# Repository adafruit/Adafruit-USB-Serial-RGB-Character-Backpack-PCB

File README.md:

## Adafruit USB Serial RGB Character Backpack PCB
&nbsp; 
<br/>
Click the image or links below to go to a specific product in the Adafruit shop.

PCB files for the Adafruit USB Serial RGB Character Backpack. Format is EagleCAD schematic and board layout
- Positive Backlight https://www.adafruit.com/product/782
- Negative Backlight https://www.adafruit.com/product/784

### DESCRIPTION
Adding a character display to your project or computer has never been easier with the new Adafruit USB or TTL serial backpack! This custom-designed PCB sits on the back of our 'standard' character LCD (16x2 or 20x4 sized) and does everything you could want: printing text, automatic scrolling, setting the backlight, adjusting contrast, making custom characters, turning on and off the cursor, etc. It can even handle our RGB backlight LCDs with full 8-bit PWM control of the backlight. That means you can change the background color to anything you want - red, green, blue, pink, white, purple yellow, teal, salmon, chartreuse, or just leave it off for a neutral background.

Inside the backpack is an USB-capable AT90USB162 chip that listens for commands both a mini-B USB port and a TTL serial input wire. The USB interface shows up as a COM/serial port on Windows/Mac/Linux. The backpack will automatically select data from whichever input is being used. For the USB connection, it will work at any baud rate. For the TTL connection, the default baud rate is 9600 but you can send it a command to set the baud rate to 2400, 4800, 9600, 19200, 28800, or 57600 baud. (The baud rate is flashed on the LCD during powerup). Any customizations such as baud rate, backlight color, brightness, splash screen, etc. are stored permanently EEPROM.

The command interface is compatible with the popular "Matrix Orbital" specifications, so this backpack will work perfectly with computer applications or libraries that are expecting a "Matrix" LCD such as "LCD Smartie". We added a few extra commands for the RGB backlight and setting the LCD size. If you don't want to use the commands, you can just start sending ASCII to the LCD and it will magically appear as typed.

This mini-kit comes with three parts: the Adafruit USB+Serial LCD backpack and a single 16x2 RGB positive or negative backlight LCD, and a strip of header. The LCD must be soldered onto the backpack using the header. This isn't a difficult task but a soldering iron and solder is required. It's easy, even for a beginner, to attach the LCD.

### License

Adafruit invests time and resources providing this open source design, please support Adafruit and open-source hardware by purchasing products from [Adafruit.com](https://www.adafruit.com)!

Creative Commons Attribution, Share-Alike license, check license.txt for more information All text above must be included in any redistribution - 
See license.txt for more information.

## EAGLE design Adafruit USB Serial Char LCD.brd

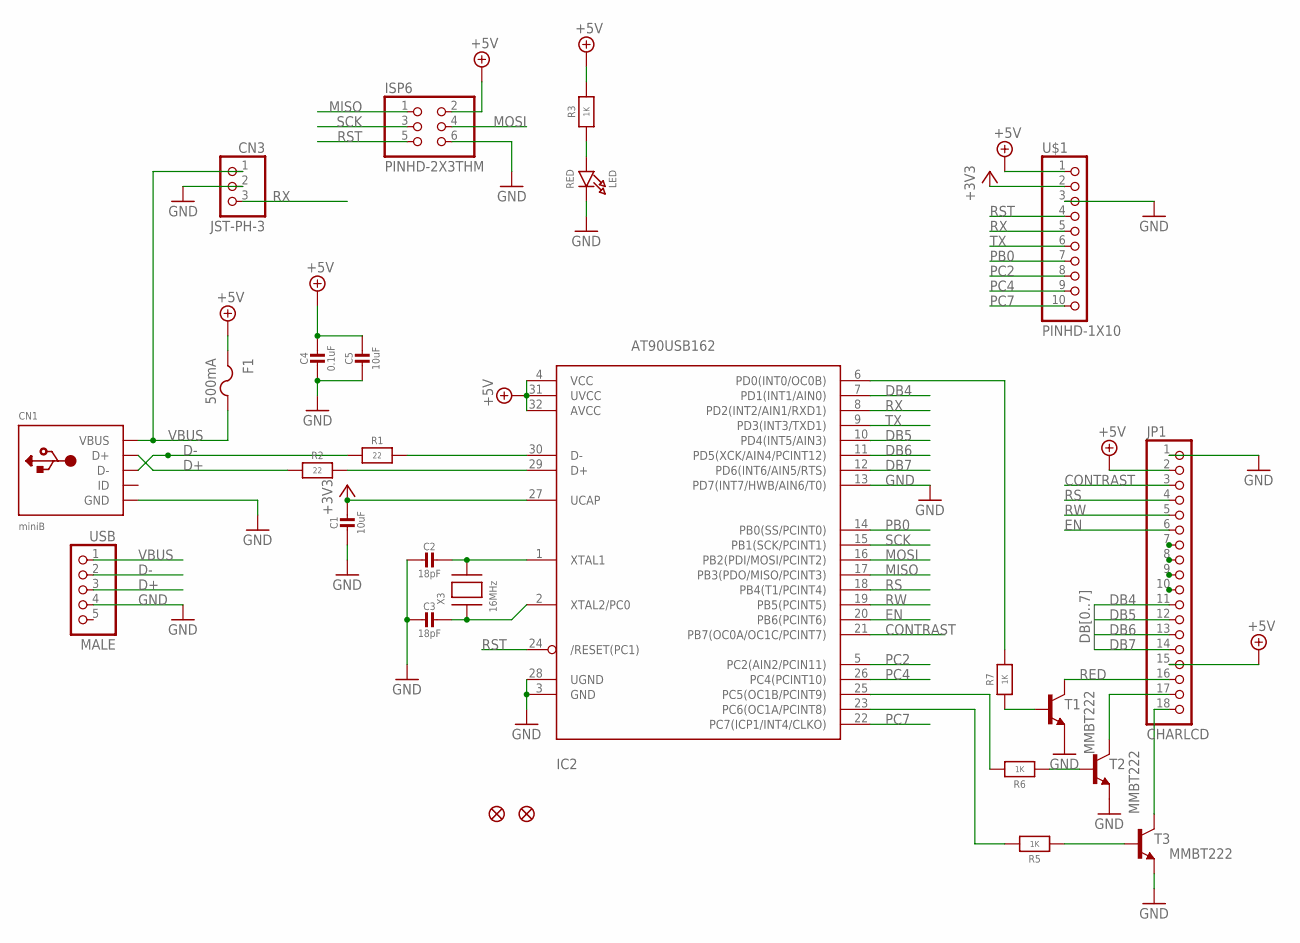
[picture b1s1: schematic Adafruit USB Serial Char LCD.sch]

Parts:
C1, C5: 10uF; 0805-NO
C2, C3: 18pF; 0805-NO
C4: 0.1uF; 0805-NO
CN1: miniB; USB-MINIB_LARGER
CN3: JST-PH-3; JSTPH3
F1: 500mA; R1206
FID1, FID2: FIDUCIAL1X2.5; FIDUCIAL-1X2.5
IC2: AT90USB162; TQFP32-08
ISP6: PINHD-2X3THM; ISP6
JP1: CHARLCD; 1X18-BIG
LED: RED; CHIPLED_0805_NOOUTLINE
R1, R2: 22; 0805-NO
R3, R5, R6, R7: 1K; 0805-NO
T1, T2, T3: MMBT222; SOT23-BEC
U$1: PINHD-1X10; 1X10-BIG
USB: MALE; 1X05
X3: 16MHz; NX5032

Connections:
+3V3: C1.1, IC2.27 (UCAP), U$1.2
+5V: C4.1, C5.1, F1.1, IC2.4 (VCC), IC2.31 (UVCC), IC2.32 (AVCC), ISP6.2, JP1.2, JP1.15, R3.2, U$1.1
BLUE: JP1.18, T3.C
CONTRAST: IC2.21 (PB7(OC0A/OC1C/PCINT7)), JP1.3
D+: CN1.D+, R2.1, USB.3
D-: CN1.D-, R1.1, USB.2
DB0: JP1.7
DB1: JP1.8
DB2: JP1.9
DB3: JP1.10
DB4: IC2.7 (PD1(INT1/AIN0)), JP1.11
DB5: IC2.10 (PD4(INT5/AIN3)), JP1.12
DB6: IC2.11 (PD5(XCK/AIN4/PCINT12)), JP1.13
DB7: IC2.12 (PD6(INT6/AIN5/RTS)), JP1.14
EN: IC2.20 (PB6(PCINT6)), JP1.6
GND: C1.2, C2.2, C3.2, C4.2, C5.2, CN1.GND, CN3.2, IC2.3 (GND), IC2.13 (PD7(INT7/HWB/AIN6/T0)), IC2.28 (UGND), ISP6.6, JP1.1, LED.C, T1.E, T2.E, T3.E, U$1.3, USB.4
GREEN: JP1.17, T2.C
MISO: IC2.17 (PB3(PDO/MISO/PCINT3)), ISP6.1
MOSI: IC2.16 (PB2(PDI/MOSI/PCINT2)), ISP6.4
unnamed: LED.A, R3.1
unnamed: R7.1, T1.B
unnamed: IC2.30 (D-), R1.2
unnamed: IC2.29 (D+), R2.2
unnamed: IC2.6 (PD0(INT0/OC0B)), R7.2
unnamed: R6.1, T2.B
unnamed: IC2.25 (PC5(OC1B/PCINT9)), R6.2
unnamed: C2.1, IC2.1 (XTAL1), X3.P$2
unnamed: C3.1, IC2.2 (XTAL2/PC0), X3.P$1
unnamed: IC2.23 (PC6(OC1A/PCINT8)), R5.2
unnamed: R5.1, T3.B
PB0: IC2.14 (PB0(SS/PCINT0)), U$1.7
PC2: IC2.5 (PC2(AIN2/PCIN11)), U$1.8
PC4: IC2.26 (PC4(PCINT10)), U$1.9
PC7: IC2.22 (PC7(ICP1/INT4/CLKO)), U$1.10
RED: JP1.16, T1.C
RS: IC2.18 (PB4(T1/PCINT4)), JP1.4
RST: IC2.24 (/RESET(PC1)), ISP6.5, U$1.4
RW: IC2.19 (PB5(PCINT5)), JP1.5
RX: CN3.3, IC2.8 (PD2(INT2/AIN1/RXD1)), U$1.5
SCK: IC2.15 (PB1(SCK/PCINT1)), ISP6.3
TX: IC2.9 (PD3(INT3/TXD1)), U$1.6
VBUS: CN1.VBUS, CN3.1, F1.2, USB.1

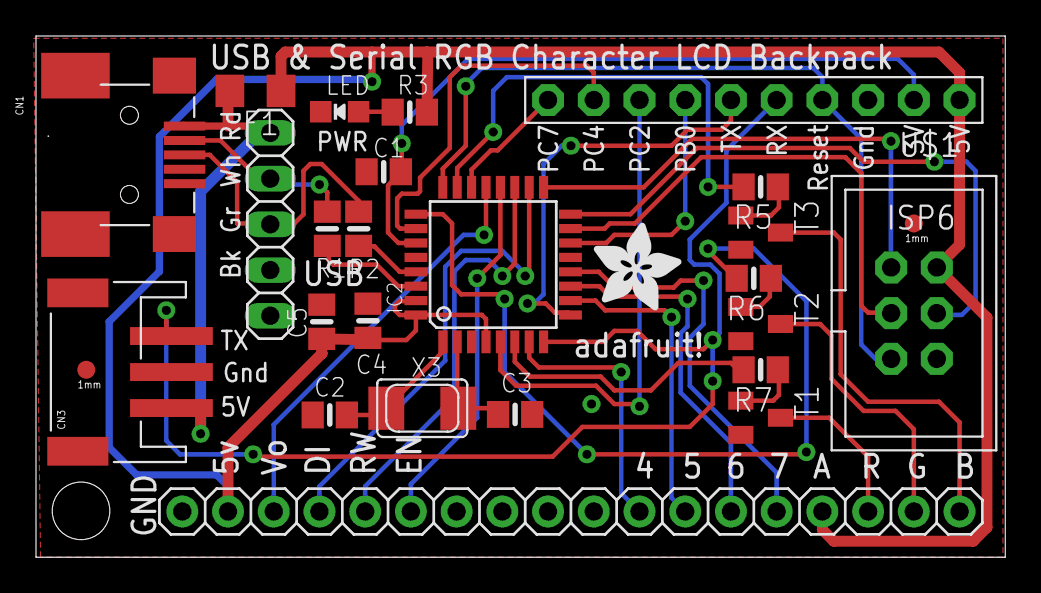
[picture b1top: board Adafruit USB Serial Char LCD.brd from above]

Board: 2 copper layers, 53.8 x 29.0 mm, 27 parts (0 on the bottom side), 38 nets.

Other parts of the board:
U$2: ADAFRUIT_5MM

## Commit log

2016-10-13 init
